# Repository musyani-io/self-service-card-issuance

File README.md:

# Self-Service Card Issuance System

Automated, secure, 24/7 student ID card distribution kiosk with a dual-controller architecture and full auditability.

## Overview

This system dispenses pre-printed student ID cards after identity verification. It is designed for unattended operation with deterministic control, mechanical safety, and a complete audit trail.

## System Architecture

Two controllers split responsibilities:

- **Raspberry Pi 5 (High-Level Control)**
  - User interface and session management
  - OTP-based authentication and policy enforcement
  - Computer vision pipeline for OCR/verification
  - Database access and audit logging

- **STM32 (Low-Level Control)**
  - Motor/actuator control and transport timing
  - Sensor acquisition (optical, limit switches, etc.)
  - Jam detection and recovery state machine
  - Hardware safety interlocks

Communication occurs over a 3.3V SPI link with a message protocol and acknowledgements to ensure safe, deterministic execution.

## Key Features

- **OTP Authentication**: SMS-based verification with configurable timeouts and retries
- **Computer Vision**: OCR-driven ID extraction with preprocessing and failure handling
- **Audit Trail**: Immutable transaction logs with timestamps and device context
- **Safety Enforcement**: Jam detection, limit checks, and fault isolation
- **Offline Tolerance**: Local caching for continued operation during network issues
- **Mock Hardware**: Back-end testing without physical hardware

## Repository Structure

- [DESCRIPTION.md](DESCRIPTION.md): Short project description and scope
- [backend/](backend/): Raspberry Pi application (auth, dispense flow, logging, DB access, communications)
- [computer_vision/](computer_vision/): CV pipeline for detection, OCR, and verification
- [hardware/](hardware/): Schematics, PCB layouts, BOMs, and EasyEDA project files
- [docs/](docs/): Research, system guidelines, and internal documentation
- [usage/](usage/): Minimal usage examples and entry points

## Data Flow (High Level)

1. User initiates session on the kiosk UI.
2. OTP is issued and verified.
3. The CV pipeline validates the card identity.
4. The Pi sends a dispense command to STM32.
5. STM32 executes the transport state machine and reports status.
6. Results and telemetry are logged.

## Hardware Integration

Hardware artifacts are organized under [hardware/](hardware/) and include:

- Schematics and PCB layouts
- BOMs and component datasheets
- EasyEDA project files

## Development Notes

- The Pi side is responsible for policies, logging, and vision.
- The STM32 side is responsible for deterministic actuation and safety.
- All dispense actions must be logged with outcome codes.

## License

See [LICENSE](LICENSE).

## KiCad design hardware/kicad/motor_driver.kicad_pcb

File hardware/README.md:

# Hardware Design and Integration

This directory contains the electrical design, PCB layout, and mechanical specifications for the self-service card issuance kiosk controller board, designed using KiCAD.

## Design Overview

The hardware implements a dual-controller architecture:

- **Raspberry Pi 5**: High-level application control, UI, vision processing, and system logging
- **STM32 Microcontroller**: Real-time actuator control, sensor acquisition, and safety interlocks
- **SPI Communication**: 3.3V differential signaling for deterministic inter-controller messaging

## Design Files

KiCAD project files are located in [kicad/](kicad/) with four independent circuit modules:

- **buck_3V3.kicad_pro**: 12V → 3.3V buck regulator for logic and STM32 supply
- **buck_5V1.kicad_pro**: 12V → 5V synchronous buck regulator (10 A) for Raspberry Pi and peripherals
- **motor_driver.kicad_pro**: High-side MOSFET drivers and PWM control for DC motor actuation
- **reverse_polarity.kicad_pro**: Input reverse-polarity protection circuit using P-channel MOSFET

Each project includes schematic (.kicad_sch), PCB layout (.kicad_pcb), and project configuration files.

## Schematic Exports

Generated schematics are exported as PDFs in the [schematics/](schematics/) directory for documentation and reference.

## PCB Layout

PCB layout files and manufacturing exports are available in [pcb/](pcb/):

- Multi-layer stackup optimized for power distribution and thermal management
- Dedicated copper area under buck regulator SW nodes for heat spreading
- Ground plane separation (PGND/AGND) with single-point Kelvin connection

## Simulations

Circuit simulations and verification are performed in [simulations/](simulations/) using Proteus (.pdsprj files) for behavioral validation of power stages and driver circuits.

## 3D Models and Renders

3D visualizations are provided in [3d/](3d/):

- Component placement and thermal analysis renderings
- PCB assembly reference

## Bill of Materials

Component lists and sourcing information:

- [bom/motor_driver.csv](bom/motor_driver.csv): Motor driver stage components

## Component Datasheets

Reference datasheets for key active components are provided in [datasheets/](datasheets/):

- Buck regulator specifications and timing parameters
- Motor driver absolute maximum ratings and thermal considerations
- Reverse-polarity MOSFET characteristics

## Design Constraints and Specifications

- **Input voltage**: 12 V nominal (fused at 10 A)
- **Output rails**: 5 V @ 8 A (Pi/display), 3.3 V @ 3 A (logic/STM32)
- **Operating mode**: 12V → 5V buck in 1 MHz forced CCM for Raspberry Pi loads
- **Safety**: Dual fusing, reverse-polarity protection, limit switch monitoring on STM32

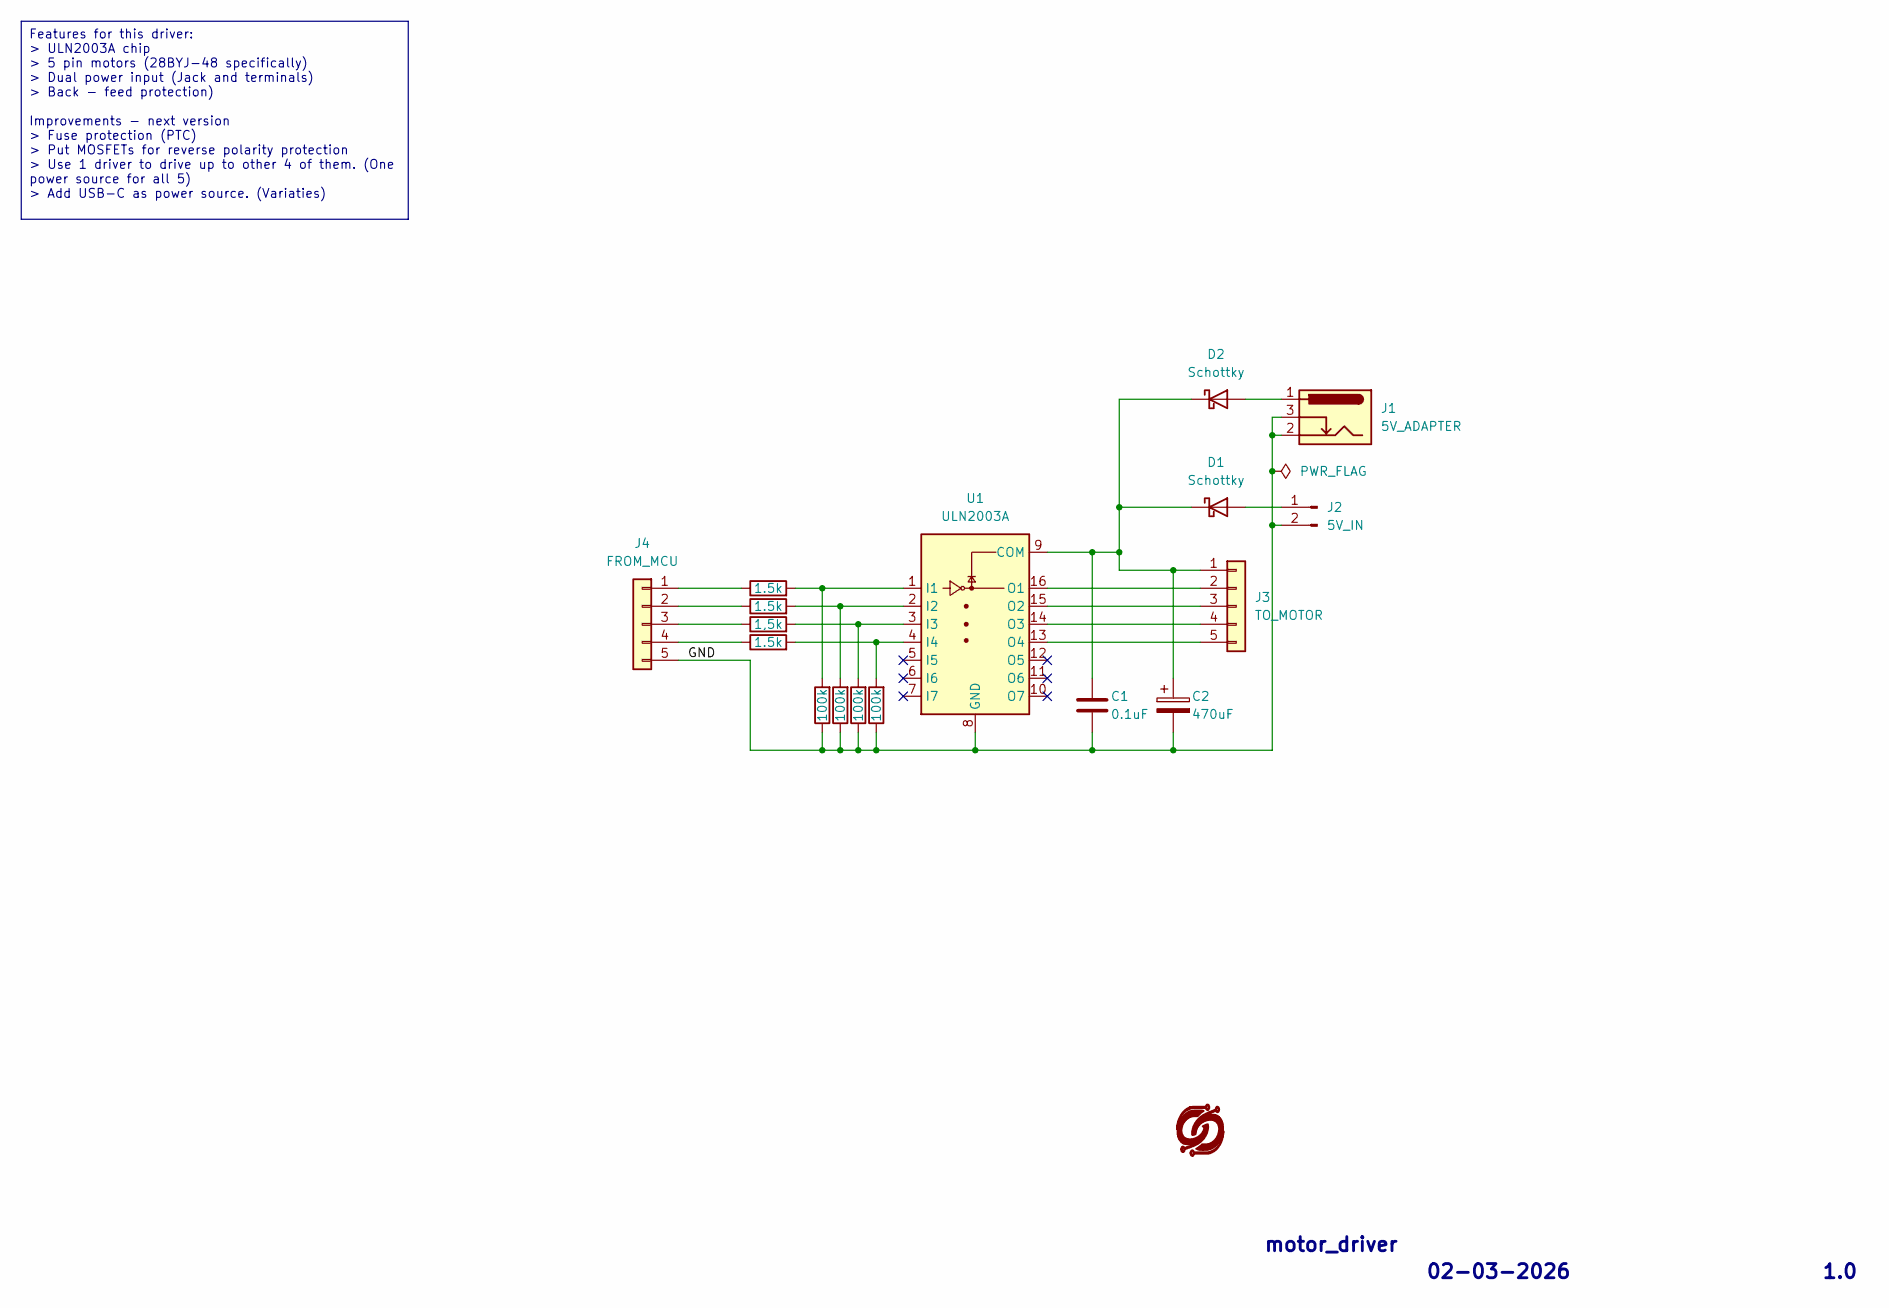
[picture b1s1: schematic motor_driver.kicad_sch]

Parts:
C1: 0.1uF; C_0805_2012Metric_Pad1.18x1.45mm_HandSolder
C2: 470uF; CP_Radial_D10.0mm_P5.00mm
D1, D2: Schottky; D_DO-201AD_P15.24mm_Horizontal
J1: 5V_ADAPTER; BarrelJack_GCT_DCJ200-10-A_Horizontal
J2: 5V_IN; PinHeader_1x02_P2.54mm_Vertical
J3: TO_MOTOR; JST_XH_B5B-XH-A_1x05_P2.50mm_Vertical
J4: FROM_MCU; PinHeader_1x05_P2.54mm_Vertical
R1, R2, R4: 1.5k; R_0805_2012Metric_Pad1.20x1.40mm_HandSolder
R3: 1,5k; R_0805_2012Metric_Pad1.20x1.40mm_HandSolder
R5, R6, R7, R8: 100k; R_0805_2012Metric_Pad1.20x1.40mm_HandSolder
U1: ULN2003A; DIP-16_W7.62mm_Socket

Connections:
/GND: C1.2, C2.2, J1.2, J1.3, J2.2, J4.5, R5.1, R6.1, R7.1, R8.1, U1.8 (GND)
unnamed: D1.2 (A), J2.1
unnamed: C1.1, C2.1, D1.1 (K), D2.1 (K), J3.1, U1.9 (COM)
unnamed: D2.2 (A), J1.1
unnamed: J3.2, U1.16 (O1)
unnamed: J3.3, U1.15 (O2)
unnamed: J3.4, U1.14 (O3)
unnamed: J3.5, U1.13 (O4)
unnamed: J4.1, R1.1
unnamed: J4.2, R2.1
unnamed: J4.3, R3.1
unnamed: J4.4, R4.1
unnamed: R1.2, R8.2, U1.1 (I1)
unnamed: R2.2, R7.2, U1.2 (I2)
unnamed: R3.2, R6.2, U1.3 (I3)
unnamed: R4.2, R5.2, U1.4 (I4)

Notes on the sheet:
Features for this driver: > ULN2003A chip > 5 pin motors (28BYJ-48 specifically) > Dual power input (Jack and terminals) > Back - feed protection) Improvements - next version > Fuse protection (PTC) > Put MOSFETs for reverse polarity protection > Use 1 driver to drive up to other 4 of them. (One po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
motor_driver
02-03-2026
1.0

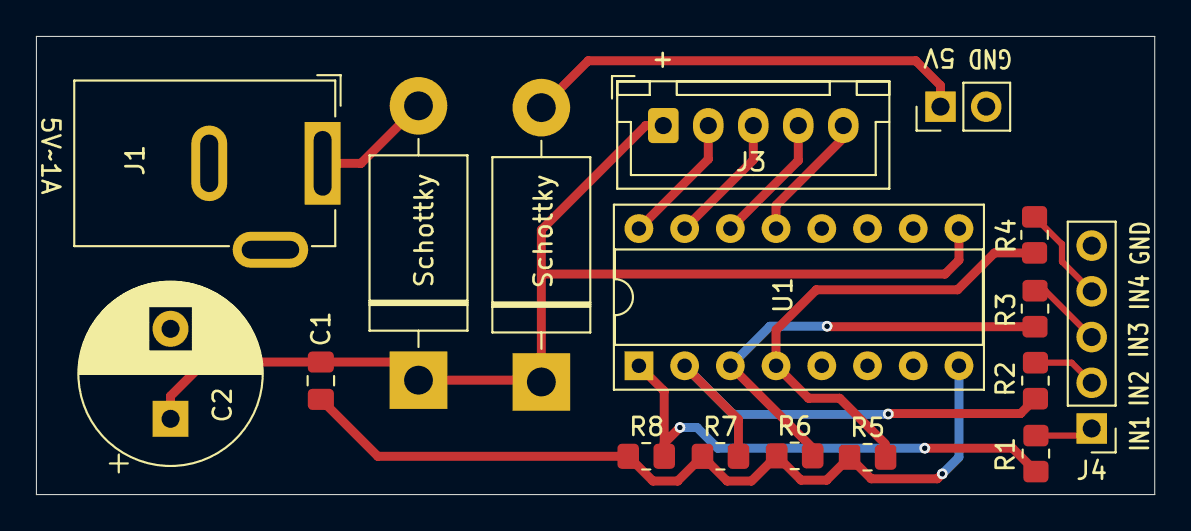
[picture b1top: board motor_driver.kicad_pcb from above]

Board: 2 copper layers, 62.1 x 25.5 mm, 17 parts (0 on the bottom side), 16 nets.

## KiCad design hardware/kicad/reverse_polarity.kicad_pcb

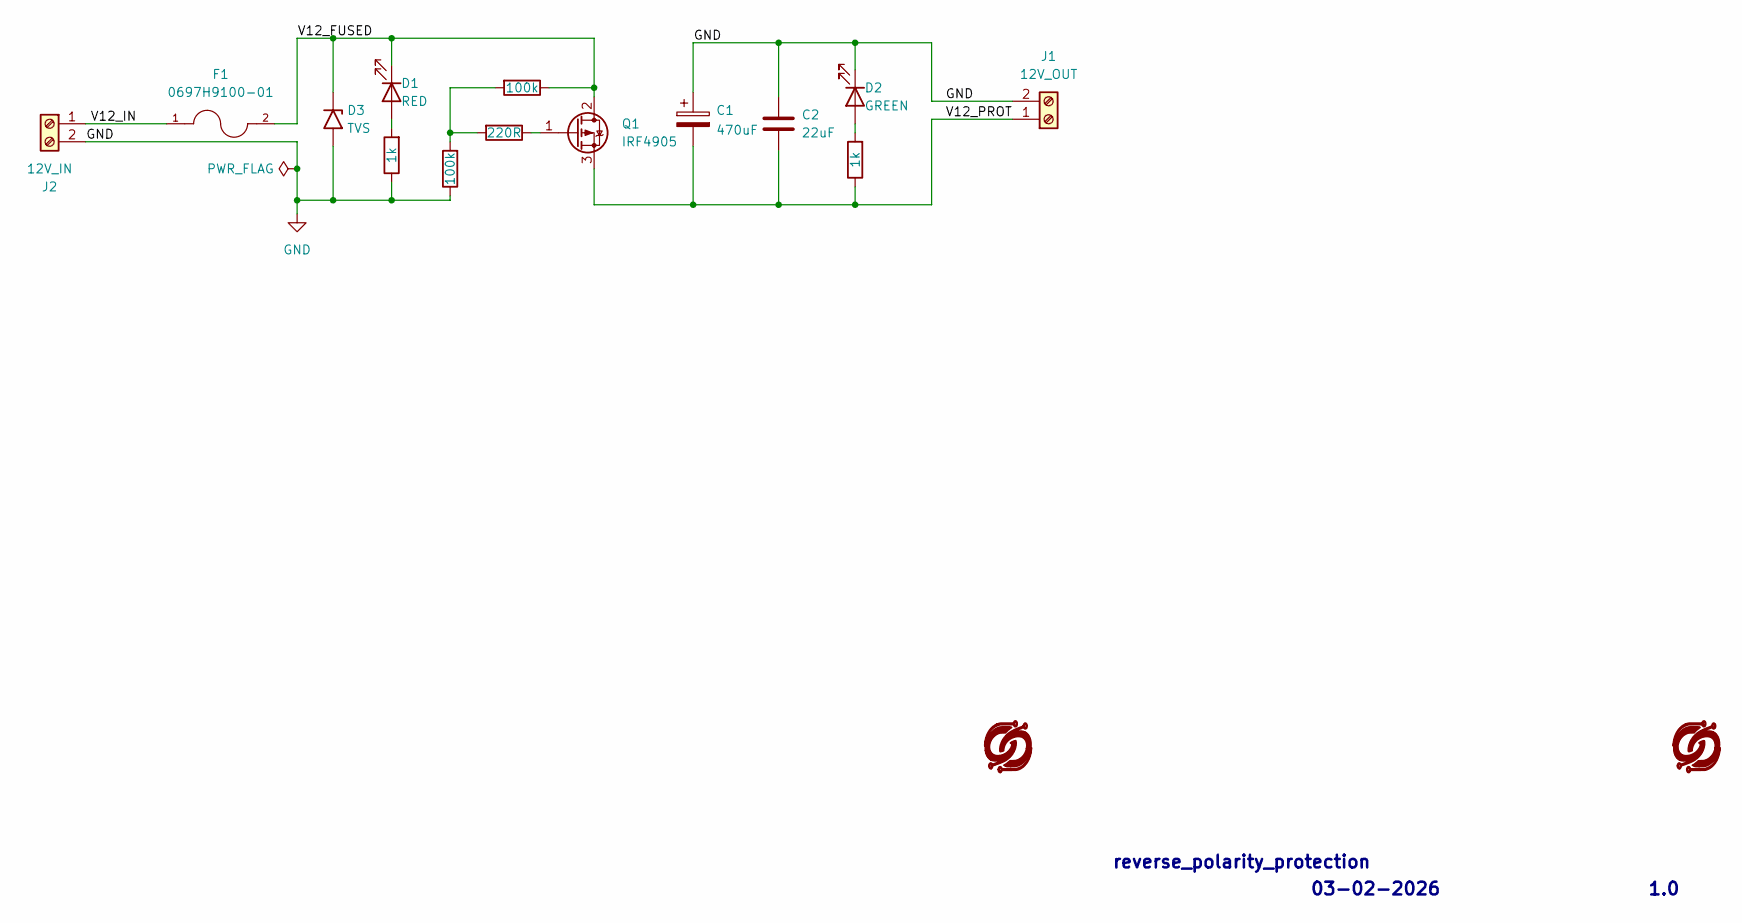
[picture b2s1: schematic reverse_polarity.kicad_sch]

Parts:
C1: 470uF; CP_Radial_D10.0mm_P5.00mm
C2: 22uF; C_0805_2012Metric_Pad1.18x1.45mm_HandSolder
D1: RED; LED_D3.0mm
D2: GREEN; LED_D3.0mm
D3: TVS; D_DO-201AE_P15.24mm_Horizontal
F1: 0697H9100-01; FUSRR508W60L835T400H810; PARTREV Jan2019
J1: 12V_OUT; CUI_TB002-500-02BE
J2: 12V_IN; CUI_TB002-500-02BE
Q1: IRF4905; TO-220-3_Vertical
R1, R5: 100k; R_0805_2012Metric_Pad1.20x1.40mm_HandSolder
R2: 220R; R_0805_2012Metric_Pad1.20x1.40mm_HandSolder
R3, R4: 1k; R_Axial_DIN0207_L6.3mm_D2.5mm_P10.16mm_Horizontal

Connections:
/V12_FUSED: D1.1 (K), D3.1 (A1), F1.2, Q1.2 (D), R1.1
/V12_IN: F1.1, J2.1
/V12_PROT: C1.2, C2.2, J1.1, Q1.3 (S), R4.1
GND: C1.1, C2.1, D2.1 (K), D3.2 (A2), J1.2, J2.2, R3.1, R5.1
unnamed: D1.2 (A), R3.2
unnamed: D2.2 (A), R4.2
unnamed: Q1.1 (G), R2.1
unnamed: R1.2, R2.2, R5.2

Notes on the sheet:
reverse_polarity_protection
03-02-2026
1.0

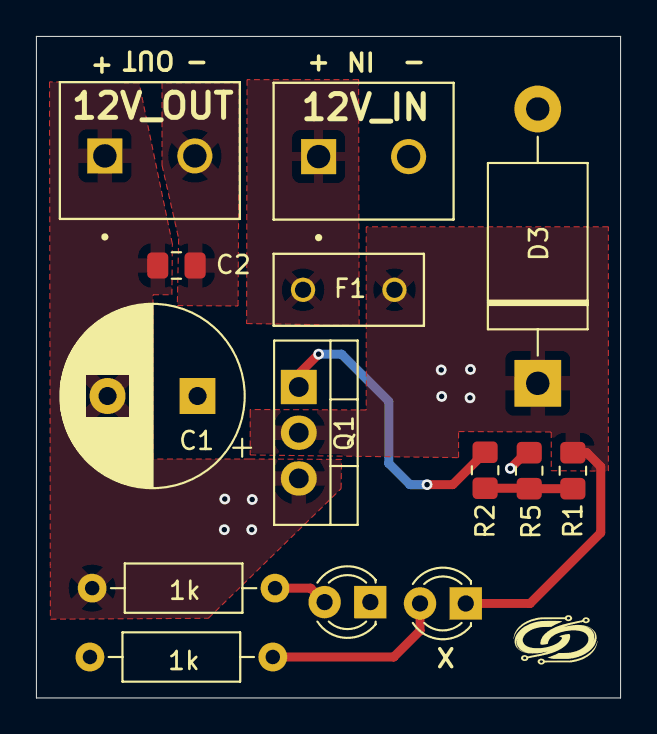
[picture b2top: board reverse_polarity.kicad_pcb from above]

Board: 2 copper layers, 32.5 x 36.7 mm, 14 parts (0 on the bottom side), 8 nets.

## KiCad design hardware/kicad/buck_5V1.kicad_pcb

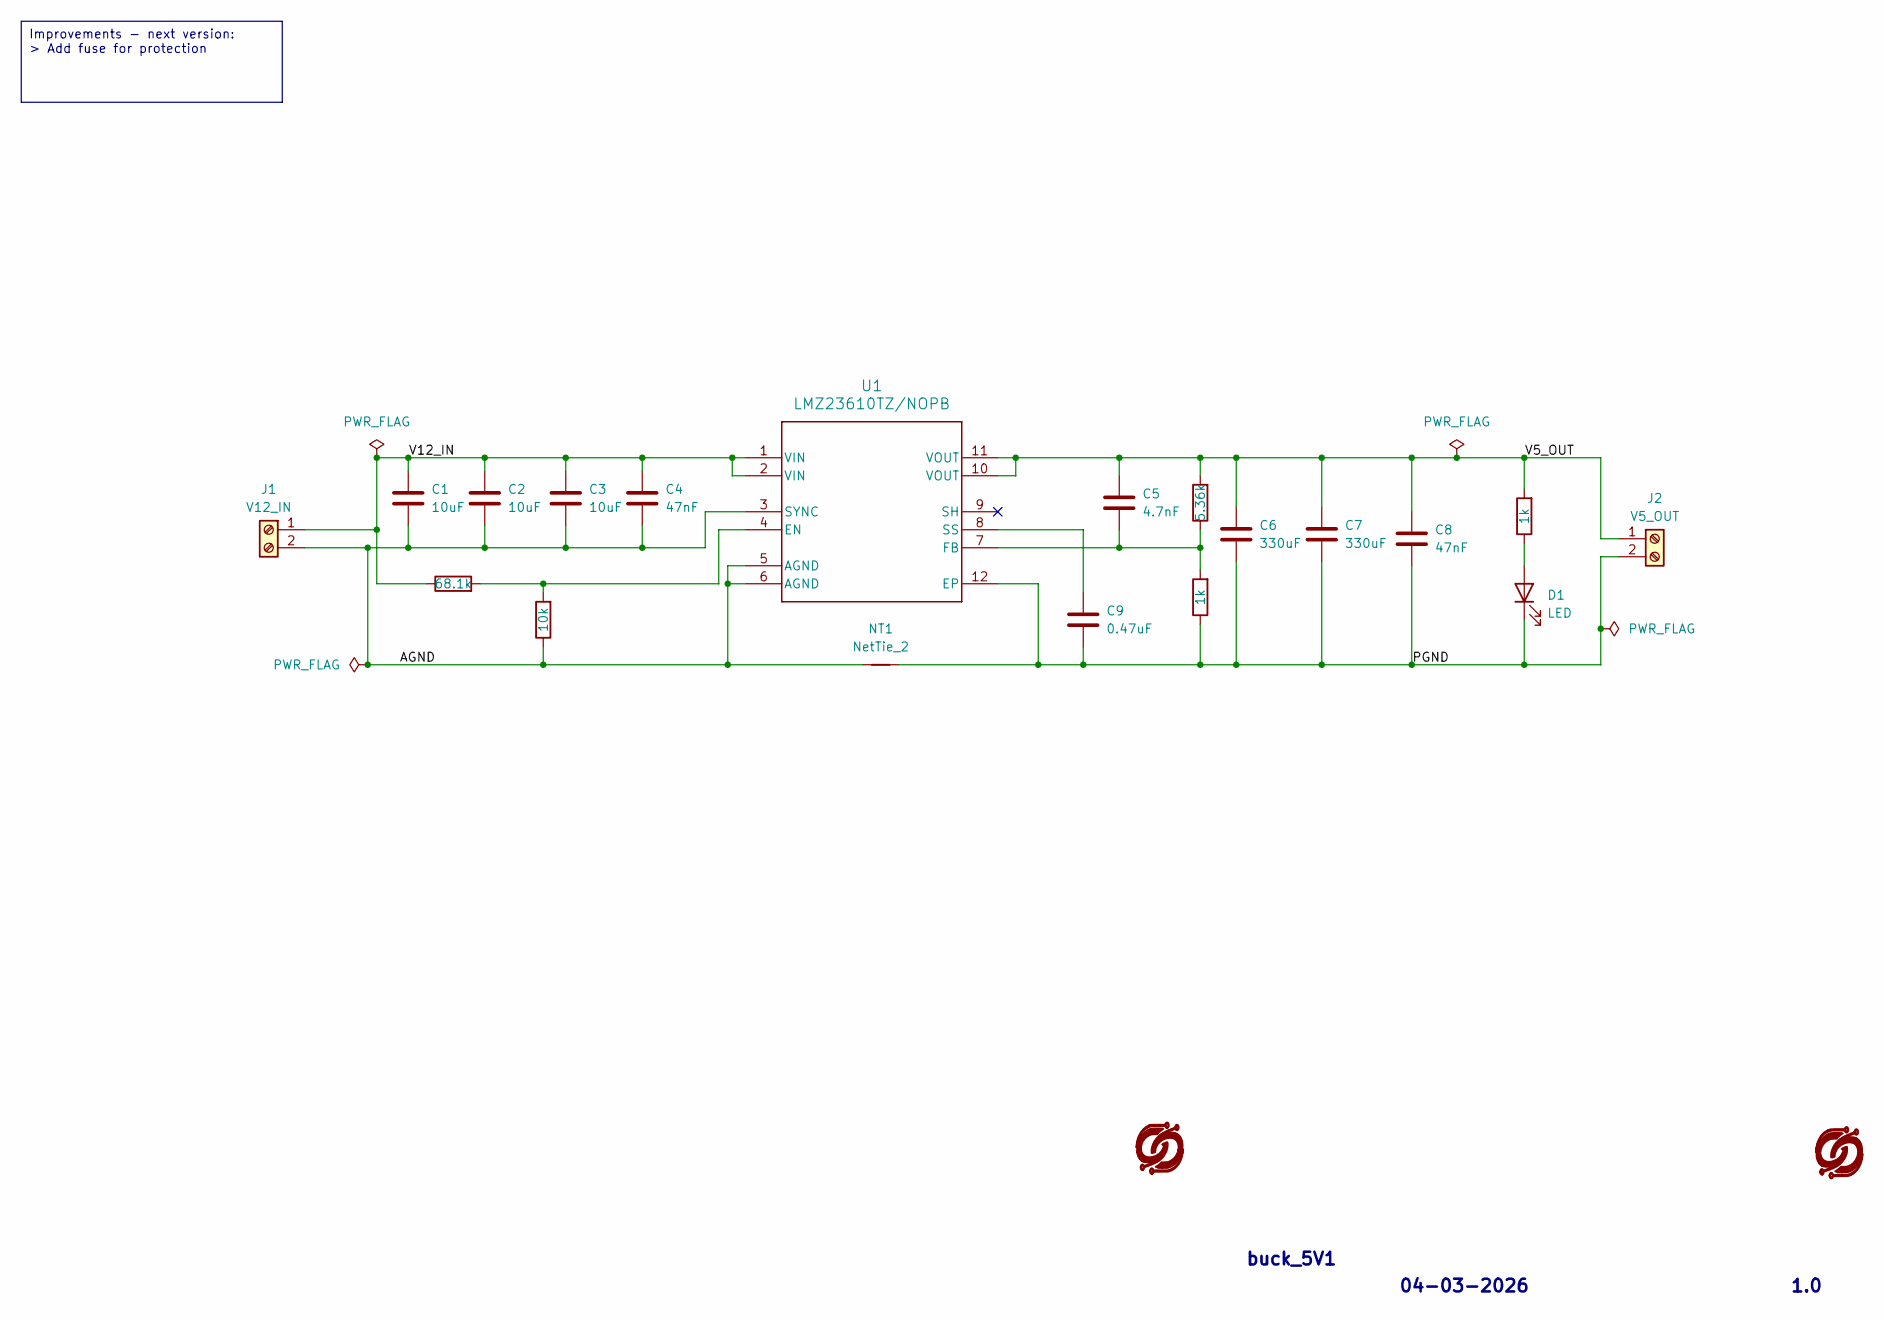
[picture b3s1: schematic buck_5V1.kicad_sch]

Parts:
C1, C2, C3: 10uF; C_0805_2012Metric_Pad1.18x1.45mm_HandSolder
C4, C8: 47nF; C_0805_2012Metric_Pad1.18x1.45mm_HandSolder
C5: 4.7nF; C_0805_2012Metric_Pad1.18x1.45mm_HandSolder
C6, C7: 330uF; C_Radial_D6.3mm_H5.0mm_P2.50mm
C9: 0.47uF; C_0805_2012Metric_Pad1.18x1.45mm_HandSolder
D1: LED; LED_D3.0mm
J1: V12_IN; CUI_TB002-500-02BE
J2: V5_OUT; CUI_TB002-500-02BE
NT1: NetTie_2; NetTie-2_SMD_Pad2.0mm
R1: 5.36k; R_0805_2012Metric_Pad1.20x1.40mm_HandSolder
R2, R4: 1k; R_0805_2012Metric_Pad1.20x1.40mm_HandSolder
R3: 68.1k; R_0805_2012Metric_Pad1.20x1.40mm_HandSolder
R5: 10k; R_0805_2012Metric_Pad1.20x1.40mm_HandSolder
U1: LMZ23610TZ/NOPB; NDY0011A_L

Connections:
/AGND: C1.2, C2.2, C3.2, C4.2, J1.2, NT1.1, R5.1, U1.3 (SYNC), U1.5 (AGND), U1.6 (AGND)
/PGND: C6.2, C7.2, C8.2, C9.2, D1.1 (K), J2.2, NT1.2, R4.1, U1.12 (EP)
/V5_OUT: C5.1, C6.1, C7.1, C8.1, J2.1, R1.2, R2.2, U1.10 (VOUT), U1.11 (VOUT)
/V12_IN: C1.1, C2.1, C3.1, C4.1, J1.1, R3.1, U1.1 (VIN), U1.2 (VIN)
unnamed: D1.2 (A), R2.1
unnamed: R3.2, R5.2, U1.4 (EN)
unnamed: C5.2, R1.1, R4.2, U1.7 (FB)
unnamed: C9.1, U1.8 (SS)

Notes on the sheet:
Improvements - next version: > Add fuse for protection
1.0
04-03-2026
buck_5V1

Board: 2 copper layers, 19 parts (0 on the bottom side), 8 nets, no tracks yet.

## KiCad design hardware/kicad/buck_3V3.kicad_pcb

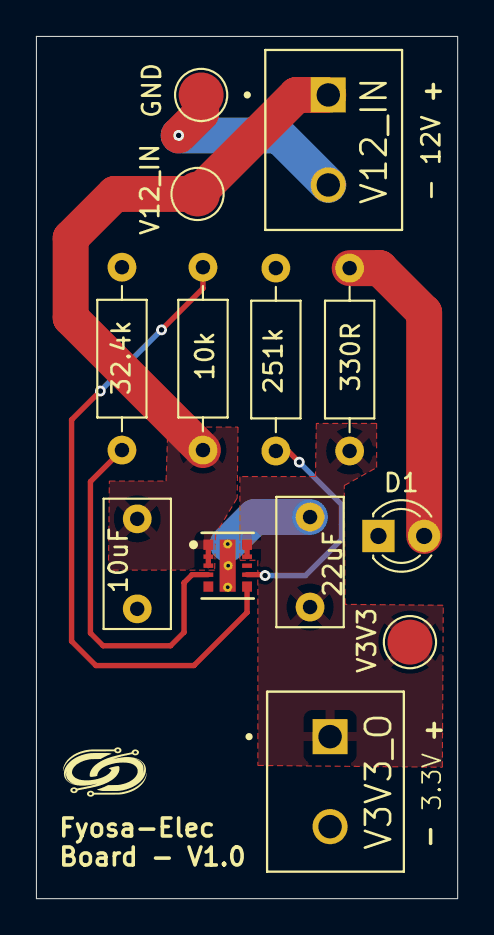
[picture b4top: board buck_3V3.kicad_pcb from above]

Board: 2 copper layers, 23.4 x 47.9 mm, 13 parts (0 on the bottom side), 7 nets.

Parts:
C1: 10uF; C_Rect_L7.0mm_W3.5mm_P5.00mm
C2: 22uF; C_Rect_L7.0mm_W3.5mm_P5.00mm
D1: LED; LED_D3.0mm
J1: V12_IN; CUI_TB002-500-02BE
J2: V3V3_O; CUI_TB002-500-02BE
R1: 32.4k; R_Axial_DIN0207_L6.3mm_D2.5mm_P10.16mm_Horizontal
R2: 251k; R_Axial_DIN0207_L6.3mm_D2.5mm_P10.16mm_Horizontal
R3: 10k; R_Axial_DIN0207_L6.3mm_D2.5mm_P10.16mm_Horizontal
R4: 330R; R_Axial_DIN0207_L6.3mm_D2.5mm_P10.16mm_Horizontal
TP1: V12_IN; TestPoint_Pad_D2.5mm
TP2: GND; TestPoint_Pad_D2.5mm
TP3: V3V3; TestPoint_Pad_D2.5mm
U1: PTSM82903SISB2R; SIS0011A-MFG

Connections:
/GND: C1.2, C2.2, D1.1 (K), J1.2, J2.2, R1.1, R2.1, TP2.1, U1.11 (GND)
/VIN: C1.1, J1.1, R3.1, TP1.1, U1.1 (VIN), U1.2 (VIN), U1.3 (EN)
/VOUT: C2.1, J2.1, R4.1, TP3.1, U1.9 (VOUT), U1.10 (VOUT)
unnamed: D1.2 (A), R4.2
unnamed: R2.2, U1.7 (FB_VSET)
unnamed: R1.2, U1.4 (MODE_S-CONF)
unnamed: R3.2, U1.6 (PG)

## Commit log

2025-12-29 Edited concept note
2025-12-29 Updated docs & README.md
2026-01-05 Updated concept note - more technical
2026-01-11 Configured paths
2026-01-11 Added important documents
2026-01-12 Updated mid-semester report
2026-01-12 Refined mid-semester report
2026-01-13 Added Gantt chart and project estimated budget
2026-01-15 Added presentation file
2026-01-16 Added panel comments
2026-01-16 Added libraries and .gitignore
2026-01-20 Added computer vision directory
2026-01-20 Complete tasks - libraries installation
2026-01-20 Added raspberry pi folder
2026-01-20 Solved panel's concern
2026-01-21 Added README.md - for CV folder
2026-01-23 Added libraries
2026-01-23 Implemented basic pre-processing functions
2026-01-23 Refined README.md and added LICENSE
2026-01-24 Advance pre-processing and its pipeline done
2026-01-24 Tested basic functions
2026-01-24 Tested advanced preprocessing
2026-01-24 Tested task 3
2026-01-24 Updated guideline file
2026-01-24 Task 4.2: Implement barcode decoding functions - decode, validate, error handling
2026-01-24 Implemented barcode tests
2026-01-24 Starting a fresh
2026-01-24 added libraries - for computer vision
2026-01-24 started CV directory
2026-01-24 implemented grayscale conversion
2026-01-24 updated cv_guideline file
2026-01-25 added resizing function
2026-01-25 edited cv_guideline.md
2026-01-26 fix: refined image error handling
2026-01-26 implemented region of interest file
2026-01-26 updated cv_readme file
2026-01-28 feat: progress report weekly
2026-01-28 feat: student_side workflow
2026-01-28 feat: system's_block-diagram
2026-01-28 feat: staff_side_workflow import
2026-02-02 feat: barcode detector code
2026-02-02 perf: resize function to both up and down scaling
2026-02-02 docs: updated task guideline
2026-02-02 feat: added barcode not found execption
2026-02-03 refactor: reformatted the code
2026-02-03 feat: added ocr detection - deleted barcode
2026-02-03 feat: set up ocr tesseract environment
2026-02-03 docs: ocr guideline documentation
2026-02-03 docs: added card layout documentations
2026-02-03 feat: card detection workflow
2026-02-03 perf: adjusted aspect ratio, image area, detection aggression
2026-02-03 docs: license edited
2026-02-04 feat: correcting perspective corners, extracting roi logic
2026-02-04 fix: replaced anchor roi
2026-02-04 fix: ocr anchor detection offsets
2026-02-04 refactor: added comments and docstrings
2026-02-04 docs: roadmap documentation - ocr
2026-02-07 feat: added OCR detection - data extraction
2026-02-08 fix: roi regions for student id
2026-02-08 docs: replaced barcode detection with ocr detection
2026-02-09 doc: documents on hardware designs
2026-02-09 doc: stm32-nucleo user manual added
2026-02-10 docs: refined ocr_guideline
2026-02-10 feat: added preprocessing functions - contrast + binarization used
2026-02-10 feat: student id validation features
2026-02-10 feat: handled ocr errors
2026-02-10 feat: implemented pipeline
2026-02-10 feat: added exceptions - pipeline
2026-02-10 feat: added a database
2026-02-10 feat: added libraries and core db access layer files
2026-02-10 feat: added kiosk schema
2026-02-10 chore: written off sensitive files
2026-02-10 feat: added api routes and schemas
2026-02-10 docs: refined readme
2026-02-10 docs: added user documentation
2026-02-10 feat: calibrator physical with GUI
2026-02-10 docs: final system - after hardware implementation
2026-02-10 fix: basic usage
2026-02-10 fix: names usage script
2026-02-10 feat: reg no extracted links to uni_db
2026-02-10 chore: added rows in kiosk db
2026-02-12 feat: started power schematic - power connector 12V
2026-02-13 feat: added 12V input protection - reverse polarity
2026-02-13 feat: bulk capacitors added - both rails
2026-02-13 docs: additional notes - power choices
2026-02-16 feat: added buck converter 12-5V logic rail - and its docs
2026-02-16 fix: refined buck converter - 12V to 5V
2026-02-16 docs: updated readme
2026-02-16 feat: added a simulation file
2026-02-17 test: tested reverse polarity protection
2026-02-18 docs: shifted from easyeda to kicad
2026-02-18 feat: power blocks design - kicad restart
2026-02-19 feat: added buck 12-5 & 12-3V3 layouts
2026-02-19 docs: refined guidelines
2026-02-19 feat: buck 12-3.3V schematic structure complete
2026-02-20 fix: changed to TPSM82903 - PG not connected yet
2026-02-20 docs: TPSM82903 datasheet added
2026-02-20 feat: mcu interfaces & motor connections
2026-02-20 feat: implemented keypad & reverse polarity protection
2026-02-21 fix: error fixing & connection config
2026-02-22 docs: added end semester report for project
2026-02-23 docs: edited student - side workflow
2026-02-23 docs: refined staff - side workflow
2026-02-23 docs: added processing - pipeline workflow
2026-02-23 doc: refined end-semester-one report
2026-02-23 chore: deleted schematic files
2026-02-23 feat: added reverse polarity circuit
2026-02-23 feat: added buck converter 12V to 3V3
2026-02-23 feat: added buck converter 12V to 5V
2026-02-24 fix: footprint issues and library conflicts - KiCAD
2026-02-24 fix: protection circuit - MOSFET & enable config
2026-02-24 feat: separated modules but added power module
2026-02-25 fix: buck connections
2026-02-27 docs: datasheet for buck converter added
2026-02-27 feat: added settings - pcb design
2026-02-27 chore: pcb board components placements
2026-02-27 chore: pcb planes filling & vias
2026-02-28 feat: added motor driver circuit
2026-03-01 feat: added reverse polarity protection
2026-03-01 feat: added motor-driver simulations
2026-03-01 perf: changed mosfet to diodes - polarity protection
2026-03-01 feat: schematic to simulation circuit - not yet simulated
2026-03-01 test: simulation went splendid
2026-03-02 feat: added pcb board and components placements
2026-03-02 perf: routed the components - PCB
2026-03-02 docs: added exports schematic & pcb
2026-03-02 docs: bom generated and updated schematics
2026-03-03 feat: implemented simulation for reverse polarity protection
2026-03-03 feat: implemented schematics of protection
2026-03-03 perf: refined protection circuit
2026-03-03 feat: added buck_5V1 schematic
2026-03-03 docs: added export schem for protection circuit
2026-03-03 feat: added buck_3V3 schematic
2026-03-03 docs: schematic export of buck converters - 12V to 5V1 & 3V3
2026-03-04 docs: edited end-semester-report
2026-03-04 feat: added pcb to buck3V3
2026-03-04 feat: added pcb for buck 5V1
2026-03-05 docs: refined end-semester-report
2026-03-05 docs: refined hardware-readme
2026-03-05 docs: added presentation for end-semester
2026-03-05 docs: added pcb export - buck_5V1
2026-03-05 docs: added pcb export - buck_3V3
2026-03-05 feat: added reverse polarity protection pcb
2026-03-06 docs: 3d files for design added
2026-03-13 fix: smd packages for reverse polarity & board orientation
2026-03-13 fix: package change & pcb comp placement - buck5V1
2026-03-13 docs: refined .gitignore
2026-03-13 docs: added project description
2026-03-15 docs: added bom, 3d & prints(pcb) - reverse polarity
2026-03-15 fix: 3d, pcb & packages - motor driver
